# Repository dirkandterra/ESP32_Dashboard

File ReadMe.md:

# _ESP_Dashboard_  

_This project uses the a CANBus and an ESP32 to drive a 2004 Dodge Intrepid Dashboard._

## How to use  

### Hardware Required  
* 2004 Dodge Intrepid Instrument Panel
* Connection:  

| Signal    | Intrepid  | ESP32 |
|-----------|-----------|-------|
| 5V        | 5V		|  5V   |
| GLDATA    | GLDATA	|  D13  |
| GLCLK     | GLCLK 	|  D14  |
| LightLatch| LightLatch|  D6   |
| Gauge CS  | Gauge CS  |  D7   |
| VFDDATA   | VFDDATA   |  D13  |
| VFDCLK	| VFDCLK	|  D14  |
| VFD Pls	| VFD Pls	|  D12  |
| Backlight | UC_LMP_DRV|  D15  |
| PB Input  | ODO PB    |  D0   |
| L Turn    | C2-5		|  D21  |
| R Turn    | C1-8      |  D22  |
| HighBeam  | C1-10     |  D23  |
| OilPress  | C2-10     |  D2   |
| ABS		| ??		|  D18  |
| Airbag    | ??		|  D19  |
| GND       | GND       |  GND  |
| CAN TX    |			|  D5	|
| CAN RX	|			|  D4	|

### Arduino Library Needed  

```
https://github.com/coryjfowler/MCP_CAN_lib.git
```

* MCP_CAN_lib

### Intrepid Dashboard Help

* Board Files:

* Intrepid Schematic (Not Complete):

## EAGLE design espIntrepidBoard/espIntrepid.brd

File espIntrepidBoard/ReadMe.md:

# _ESP_Dashboard_  

_This project uses the a Nano with a MCP2515 to drive a 2004 Dodge Intrepid Dashboard._

## How to use  

### Hardware Required  
* 2004 Dodge Intrepid Instrument Panel
* Connection:  

| Signal    | Intrepid  |ESP8266|
|-----------|-----------|-------|
| 3.3V      | NC		| VCC	|
| SCLK      | D0(SCL)   | GPIO14|
| VFDCLK	| VFDCLK	| Trans	| 
| MOSI      | VFD/GLDATA| GPIO13|
| Gauge CS  | Gauge CS  | GPIO16|
| Light Pls | Light Pls | GPIO12|
| VFD Pls	| VFD Pls	| GPIO02|
| GND       | GND       | GND   |

### Configure the project  

```
make menuconfig
```

* Set serial port under Serial Flasher Options.

### Build and Flash  

Build the project and flash it to the board, then run monitor tool to view serial output:

```
make -j4 flash monitor
```

(To exit the serial monitor, type ``Ctrl-]``.)

See the Getting Started Guide for full steps to configure and use ESP-IDF to build projects.

## Example Output  

* LOG:  

```
I (233) spi_oled: init gpio
I (235) gpio: GPIO[12]| InputEn: 0| OutputEn: 1| OpenDrain: 0| Pullup: 1| Pulldown: 0| Intr:0
I (239) gpio: GPIO[15]| InputEn: 0| OutputEn: 1| OpenDrain: 0| Pullup: 1| Pulldown: 0| Intr:0
I (251) spi_oled: init hspi
I (257) spi_oled: init oled
```

* Intrepid Schematic (Not Complete):

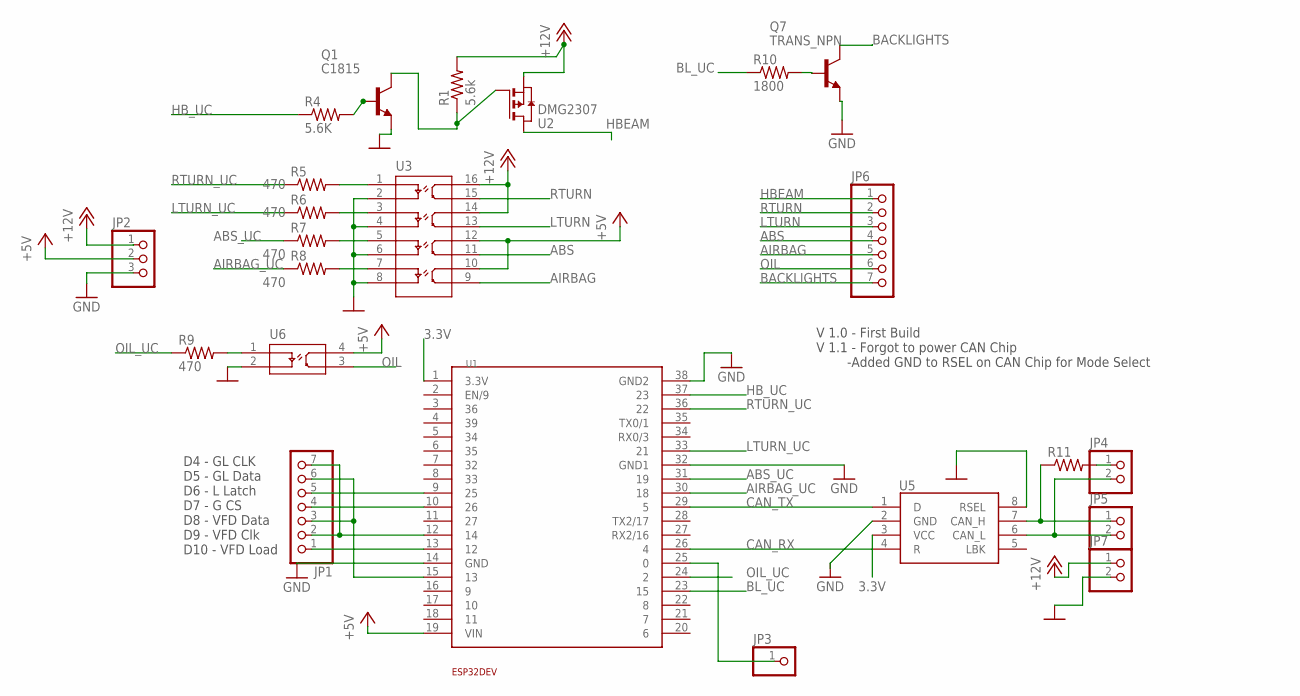
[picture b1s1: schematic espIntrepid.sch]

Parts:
JP1, JP6: PINHD-1X7; 1X07
JP2: PINHD-1X3; 1X03
JP3: PINHD-1X1; 1X01
JP4, JP5, JP7: PINHD-1X2; 1X02
Q1: C1815; SOT-23
Q7: TRANS_NPN; SOT-23
R1: 5.6k; M1206
R4: 5.6K; M1206
R5, R6, R7, R8, R9: 470; M1206
R10: 1800; M1206
R11: R-US_M1206; M1206
U1: ESP32DEV_38
U2: DMG2307; SOT-23
U3: LTV-847; SM-16
U5: SN65HVD233D; SOIC-8
U6: LTV-817; SM-4

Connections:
3.3V: U1.1 (3.3V), U5.3 (VCC)
+5V: JP2.2, U1.19 (VIN), U3.10, U3.12, U6.4
+12V: JP2.1, JP7.1, R1.2, U2.2 (S), U3.14, U3.16
ABS: JP6.4, U3.11
ABS_UC: R7.1, U1.31 (19)
AIRBAG: JP6.5, U3.9
AIRBAG_UC: R8.1, U1.30 (18)
BACKLIGHTS: JP6.7, Q7.3 (C)
BL_UC: R10.1, U1.23 (15)
CAN_RX: U1.26 (4), U5.4 (R)
CAN_TX: U1.29 (5), U5.1 (D)
GND: JP2.3, JP7.2, Q1.2 (E), Q7.2 (E), U1.14 (GND), U1.32 (GND1), U1.38 (GND2), U3.2, U3.4, U3.6, U3.8, U5.2 (GND), U5.8 (RSEL), U6.2
HBEAM: JP6.1, U2.3 (D)
HB_UC: R4.1, U1.37 (23)
LTURN: JP6.3, U3.13
LTURN_UC: R6.1, U1.33 (21)
unnamed: Q7.1 (B), R10.2
unnamed: R5.2, U3.1
unnamed: JP5.1, R11.1, U5.7 (CAN_H)
unnamed: JP1.5, U1.9 (25)
unnamed: JP1.4, U1.10 (26)
unnamed: JP1.1, U1.13 (12)
unnamed: JP1.3, JP1.6, U1.15 (13)
unnamed: JP1.2, JP1.7, U1.12 (14)
unnamed: R8.2, U3.7
unnamed: Q1.1 (B), R4.2
unnamed: Q1.3 (C), R1.1, U2.1 (G)
unnamed: R6.2, U3.3
unnamed: R7.2, U3.5
unnamed: R9.2, U6.1
unnamed: JP3.1, U1.25 (0)
unnamed: JP4.2, JP5.2, U5.6 (CAN_L)
unnamed: JP4.1, R11.2
OIL: JP6.6, U6.3
OIL_UC: R9.1, U1.24 (2)
RTURN: JP6.2, U3.15
RTURN_UC: R5.1, U1.36 (22)

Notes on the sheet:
D4 - GL CLK D5 - GL Data D6 - L Latch D7 - G CS D8 - VFD Data D9 - VFD Clk D10 - VFD Load
V 1.0 - First Build V 1.1 - Forgot to power CAN Chip -Added GND to RSEL on CAN Chip for Mode Select

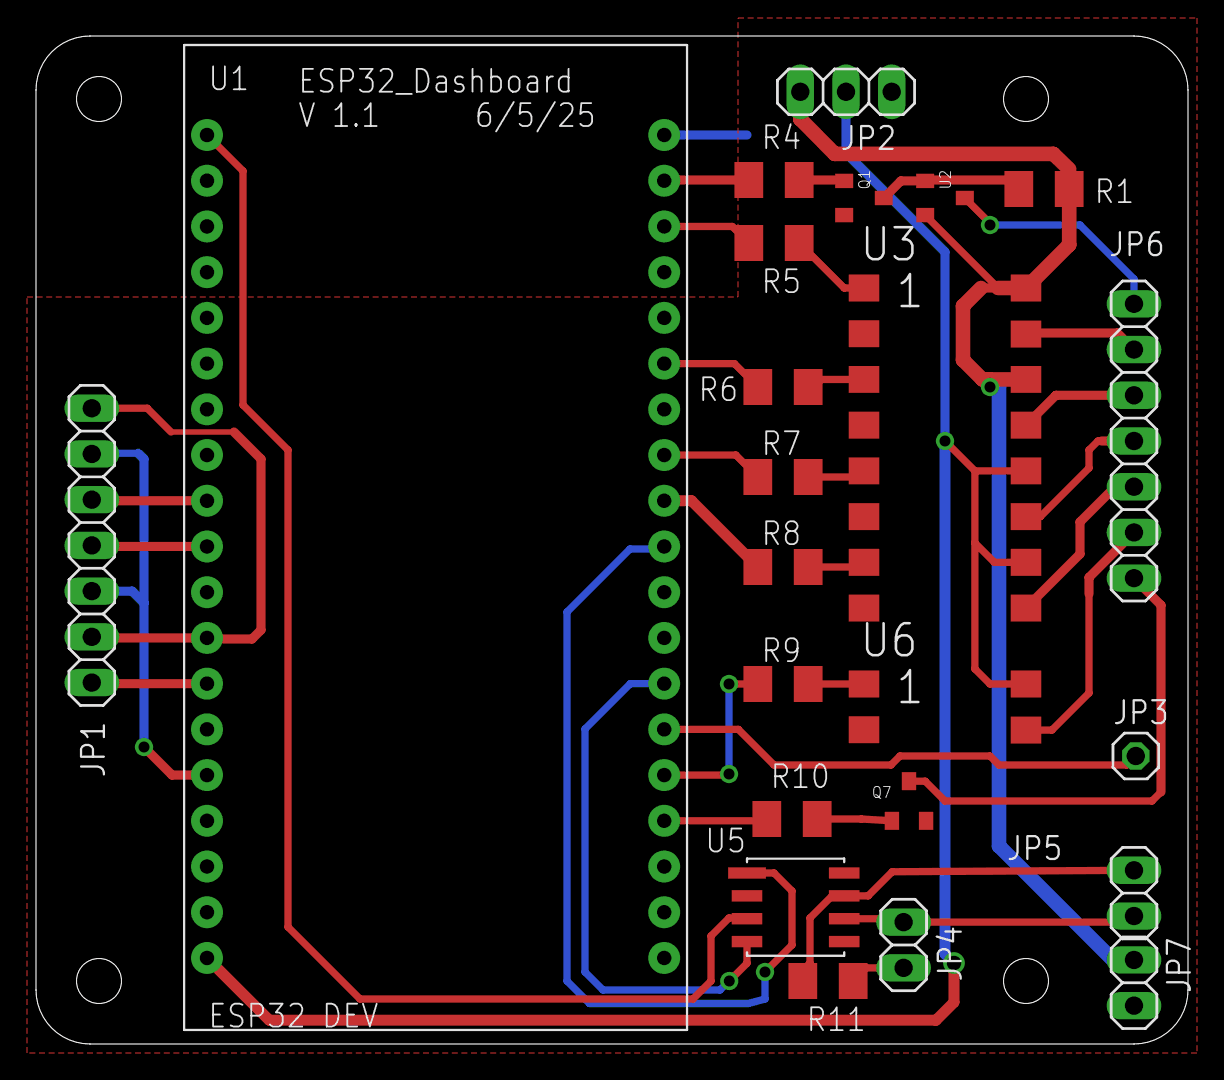
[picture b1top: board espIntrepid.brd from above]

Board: 2 copper layers, 64.0 x 56.0 mm, 23 parts (0 on the bottom side), 37 nets.

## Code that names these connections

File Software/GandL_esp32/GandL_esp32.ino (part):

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
#define VER "1.00"

#define HBEAM   23
#define RTURN   22
#define LTURN   21
#define ABS     19
#define AIRBAG  18
#define OIL     2
#define BKLIGHT 15
#define PB      0

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void setup() {
  int ii=0;
  pb.lastRead = !PB_PUSHED;
  pinMode(HBEAM,OUTPUT);
  pinMode(RTURN,OUTPUT);
  pinMode(LTURN,OUTPUT);
  pinMode(AIRBAG,OUTPUT);
  pinMode(ABS,OUTPUT);
  pinMode(OIL,OUTPUT);
  pinMode(BKLIGHT,OUTPUT);
  pinMode(PB,INPUT);

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
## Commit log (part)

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2024-12-11 First Upload switching from nano
    Changed board to ESP32
2024-12-11 removed unneeded nano mcp2515 files
2024-12-15 Started board routing
2025-02-10 Using optoisolators
2025-02-11 Still need to test but board finished
2025-02-11 Created esp32 arduino program
2025-02-11 Added SPI routines to handle Guage,vfd, and lights
2025-02-11 Made improvements to board (small stuff)
2025-02-12 SPI working
2025-02-12 -Redefined some non-returning functions, partly working now
2025-02-14 Making progress, no VFD but partly guage and 100% lights
2025-02-15 Update RS232Decode.cpp, gauge routine had an error
2025-02-15 All functioning with ESP32, just trying to get rid of the 'ticking' bug from the guages
2025-02-15 Software is fully functional. Lights need SPI Mode1 (clock falling edge) Guage and VFD need Mode0 (clock rising edge)
2025-02-17 Finished board
2025-05-29 Generated PDF and updated readme
2025-05-29 Readme
2025-05-29 Forgot pdf
2025-05-29 fixed readme
2025-06-06 Made fixes to board, started V1.1
2025-06-07 -Swapped 2 pins on board -Added reverse engg schematic
2025-12-09 Tweaked coolant and fuel gauge math
2025-12-14 Forecast working
2026-04-29 Found an issue with glitchy VFD, had to do with sending vfd dimming
2026-04-29 Separating out EE and MQTT
2026-04-29 compiles now
2026-05-02 A few tweaks to get vfd better on blanking
2026-05-02 testing VFD and tick issue
2026-05-07 Brought in improvements from main
